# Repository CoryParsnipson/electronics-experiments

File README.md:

# electronics-experiments

Educational and experimental PCB designs for Raspberry pi related products and peripherals

## Project List

### [555-timer-pwm-with-digipot](./555-timer-pwm-with-digipot)

This is a hardware PWM output generator. This will give you a fixed frequency, variable duty-cycle PWM signal without using a microcontroller. This uses a 555-timer in astable oscillation mode that provides a 5% - 100% duty cycle. This allows you to control small motors and dim LED lights (see `ap5726-lcd-backlight-driver`).

### [ap5726-lcd-backlight-driver](./ap5726-lcd-backlight-driver)

This is a breakout board for testing the AP5726 white-LED driver (used for driving 5-7in LCD screen modules). This DC-DC converter is specifically designed to drive LEDs in series while supplying a constant 40mA current and up to 35V.

### [as01808ao-enclosure](./as01808ao-enclosure)

This is an experiment to mount an AS01808AO micro speaker to a PCB and have 3d printed enclosure parts bolted on. It works surprisingly well.

### [attiny-402-i2c-pwm-generator](./attiny-402-i2c-pwm-generator)

This is a project to use the new ATTiny series microcontroller to make an I2C controlled PWM signal that can be varied by frequency and duty cycle.

### [max98357-amp](./max98357-amp)

This is a design for a Class D speaker amplifier based on a [product by Adafruit](https://learn.adafruit.com/adafruit-max98357-i2s-class-d-mono-amp).

### [mipi-dsi-breakout](./mipi-dsi-breakout)

This is a pcb design that acts as an adapter board to hook up DSI signals coming from a LCD module with MIPI DSI interface to the raspberry pi.

### [retrocution-usb-hub](./retrocution-usb-hub)

The usb hub design uses an FE1.1s integrated USB 2.0 controller with the board layout heavily referenced from [Retrocution](https://www.retrocution.com/2020/01/15/easy-diy-tiny-usb-hub-for-raspberry-pi-projects/). Many thanks to Retrocution!

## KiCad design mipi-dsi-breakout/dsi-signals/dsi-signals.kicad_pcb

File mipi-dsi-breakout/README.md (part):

# mipi-dsi-breakout 

This design is intended to interface with different MIPI DSI LCD screens and route the DSI signals to a Raspberry Pi.

## KiCAD Version

Current version: KiCAD 9.0.3

This was originally made with KiCAD 9.0.3.

## Credits

Massive thanks to aBUGSworstnightmare and 6by9 of the Raspberry Pi Forums for help debugging and many factual and editorial corrections to this README. The debugging and driver/software stage of this project would not be possible without their help.

I am also thankful for the help and support from members of the SomthingAwful forums: babyeatingpsychopath, cakesmith handyman/bad dragon breath, Seat Safety Switch, Granite Octopus, Sgt Fox, ihafarm, HazCat, BlackTie, and many more.

## Sponsorship

The PCB fabrication for this project is sponsored by [PCBWay](https://www.pcbway.com/). PCBWay is a manufacturer of printed circuit boards and they also offer services such as PCB assembly, 3D printing plastic and metal, and much more. Their online quote system and thorough customer service made this design a breeze to order.

## Description

When working with microcontrollers or single board computers (SBC), you can buy "all-inclusive" LCD screen kits from electronics hobby stores that are basically plug and play. With this, the user experience is quite nice, needing only to plug in a video cable going from the LCD screen circuitry directly to the microcontroller or SBC. However, these kits leave little flexibilty terms of physical form factor, size and type of LCD screen, and price.

This project is an attempt to go beyond the beginner LCD peripherals offered by electronics hobby stores and interface directly with an LCD screen using custom peripheral circuitry. The hope is to increase the available LCD screens one can use beyond the small selection specifically available for a particular ecosystem of microcontroller or SBC products.

### Background and Context

An existing product like the [OSOYOO 5 inch DSI LCD Screen for Raspberry Pi](https://www.amazon.com/OSOYOO-Touchscreen-Monitor-Raspberry-800%C3%97480/dp/B0CWL7R8T4) was used as a reference base. This is a 5 inch screen that is designed to work out of the box with the Raspberry Pi family of products.

It is desirable for the following feaures:

* Built in touch screen
* Uses the DSI interface to transfer data (no need to use up an HDMI, USB, or GPIO pins to hook up)
* Supported out of the box by Raspberry Pi OS (no need to install external drivers)

It falls short due to:

* Relatively high price (~$50, too high for production runs)
* Large physical form factor (it is approximately 10 mm thick, permanently glued to a PCB, and contains metal standoffs which limit including it in a portable electronics device)
* Limited to 5 inch LCD screen and resolution from manufacturer

The objective of this project is to prototype something that could potentially replace this product while allowing one to swap the screen out and adjust the PCB design.

### Design Overview

For context into how this fits into a larger project, refer to the following block diagram:

Here we can see a motherboard for a Raspberry Pi Compute Module. This is a development board that you can use just like a regular computer once you hook up a keyboard, mouse, monitor, and power cord into it.

On the right, there is a section labeled "LCD Screen" (imagine that it is the OSOYOO screen). Described in 4 numbered functional blocks surrounding the screen component is the peripheral circuitry required to connect the LCD screen to the microcontroller.

Assuming that everything is built and working, we should be able to see the operating system graphical output on the LCD screen as if we were using it as a computer monitor. This project is a PCB implementation of the functional blocks labelled (1) and (4).

For information about implemting blocks (2) and (3), see the other projects in this repository, [ap5726-lcd-backlight-driver](/ap5726-lcd-backlight-driver) and [attiny-402-i2c-pwm-generator](/attiny-402-i2c-pwm-generator) respectively.

### LCD Screens Overview

The LCD screens this project is concerned with are mostly *Thin Film Transistor* (TFT) screens. See [this page](https://www.topwaydisplay.com/en/blog/how-tft-lcd-works-explained) to learn more about how TFT screens work. Essentially, TFT LCDs are a VLSI design that prints individual transistors on a transparent substrate that act as individual pixels. So the takeaway here is that it is not very simple or inexpensive to produce these, and that there are very expensive foundries needed to manufacture these like one would need to make CPUs and other integrated circuits, though a TFT screen does not require as small transistors nor is the design as complex as a CPU.

*Left: segmented (monochrome, big segments) Middle: dot matrix (monochrome, medium resolution) Right: TFT (graphical, transistors, RGB color)*

When searching for LCD screens one must be careful to specify which kind, between a segmented display, dot matrix, or a fully graphical screen. Here we want graphical displays.

Within the graphical LCD displays are Twisted Neumatic (TN) and In-Plane Switching (IPS) type displays with the difference being that IPS displays are more vibrant, brighter, and have a better viewing angle range than TN displays, which are older and cheaper than IPS displays.

There are also Organic LED (OLED) screens now, which are a different technology where VLSI LEDs are printed directly onto a substrate instead of whatever circuitry and electrodes TFT screens use. OLED screens are even more vibrant, have true black color, and supposedly use less energy because each pixel that is turned off does not consume power. These screens are better in every way, but are still relatively new and thus more expensive and less available. Now you have AMOLED screens which are minor improvements upon an OLED screen but mostly the same thing.

> NOTE: as of the time of this writing, if you try to buy an OLED screen from an electronics supplier, you may find very (physically) small, extremely low resolution, monochrome screens that have more in common with segmented displays or something you'd see in an old calculator. If you want a *graphical* OLED screen, you would need to specifically search for it, or try to get an AMOLED screen instead. Still, these are not as common as IPS displays.

### Overview of LCD Interfaces

If that wasn't complicated enough, one must also have to worry about the interface of the LCD screen, and there are many different interface protocols. Some of the more common ones:

* HDMI
* MIPI DSI
* LVDS
* SPI
* RGB/MCU/Parallel/DPI

#### HDMI

This might be the most popular screen interface. With an HDMI controller, the screen hooks up to a host using an HDMI cable. This makes it compatible with anything that supports the HDMI protocol, and not just a specific device. It also supports audio and input signals as well. This seems to be the most popular interface type for LCD screens around 5 inches in size, so it would give us the best options for screens.

Some of the disadvantages are the relatively complicated (and physically large) circuitry required, and the extra power consumption from converting from whatever format the LCD screen is in natively to HDMI. For these reasons, the search for screens for this project was limited to MIPI DSI.

> NOTE: in a "real" product development environment, what probably happens is that the designer will look for screens with the required attributes, and then integrate whatever interface the desired product was using afterwards. Going forward, this is probably a much better attitude than choosing the interface first.

#### MIPI DSI

MIPI DSI stands for *Mobile Industry Processor Interface Display Serial Interface*. For this project specifically, we have chosen to look for DSI screens exclusively because the DSI interface is convenient for Raspberry Pi products. Having a DSI screen uses less power, supports higher resolutions and refresh rates, low physical profile, and does not take up GPIO or other ports that could be used for other things. The DSI protocol is also meant for internal connectors for mobile and low power and physical small devices.

#### LVDS

"Low Voltage Differential Signaling" actually refers to the transmission method and not an entire protocol, so it is not quite equivelant to other things on this list. This term is usually kind of an umbrella term to refer to commercial or closed-source devices which have their own prioprietary protocol running on top of the LVDS transmission layer. This is common for larger screens such as for laptops and tablets. It is generally not recommended to use a screen that claims to use LVDS because it is hard to reverse engineer or find documentation on proprietary protocols, especially since they would be completely different across screens.

#### SPI

Serial Peripheral Interface (SPI) is a protocol used for many devices, not just screens. This is common for graphical LCD screens 3-4 inches and smaller, since the maximum data rate for SPI is not very fast. Even then, you may observe that the framerate is not very high due to the transfer rate limitations. Furthermore, an SPI screen will probably require more CPU overhead and power because the protocol is not designed specifically to transmit video. One good thing is that the interface and protocol is very simple, so it is very easy to integrate into a device as long as the screen is small and the framerate and resolution is not too large.

SPI devices usually hook in through GPIO pins.

#### RGB/MCU/Parallel/DPI

Display Parallel Interface (DPI) uses many more GPIO pins and as such the parallel configuration allows for much higher resolution or faster framerate than SPI devices do. It still suffers from similar power and CPU overhead limitations, but on the Raspberry Pi, there is a dedicated hardware block for driving DPI so aside from the GPIO usage, there is no overhead. For example, in a Raspberry Pi, hooking up a DPI screen may use almost all of the 40 available GPIO pins. This is not convenient if one wants to integrate multiple peripherals to the same Raspberry Pi or other GPIO limited device.

## Part Selection

### LCD Screen Parts

Finding LCD screen modules that are not part of a kit directly from manufacturers is tough. Lots of the supply is only available from China.

There were three main websites explored in my search for screens:

1. [Aliexpress](https://www.aliexpress.us)
   While not the most user friendly place, it contained the largest and relevant selection. I ended up buying all screens I wanted to try out from here. The "negotiation" process of talking to different salespeople to get a list of parts with the required specs was long and tedious. The pricing shown is not always accurate, but you can haggle with them. The price is dependent on the quantity you buy, which is usually a minimum of 500 or 1000 pieces, but you can order a few samples for a higher price for development (which is what I did).

1. [Waveshare](https://www.waveshare.com)
   This is more of a general electronics shop like Adafruit or SparkFun. For places like these, screen selection is very small, but the quality of parts is much better. The price is retail price, so not really ideal, but would still work for prototyping and development.

1. [BuyDisplay](https://www.buydisplay.com)
   This is another website that specializes in displays. The selection is large (but not as large as Aliexpress), and contains lots of unique parts.

#### Search Criteria

I was looking for a graphical, full color LCD screen that was around 5 inches across. Resolution around 480x800 or slightly higher is fine. The difficult part was finding parts with a MIPI DSI interface, which aren't very common especially on smaller screens. Looking at nits (>= 200) is a nice to have, to get an idea of whether or not the screen would be visible outdoors. A capactive touch screen was also a nice to have. If the screen comes with a touch panel, you can also ask them to customize the shape of the front lens/sticker if you order in bulk. This could be useful when putting together a complete product.

#### 4.3 Inch 480x800 MIPI DSI Display with CTP

The New Nintendo 3DS (non XL) top screen is about 4 inches across, and I think that is a nice size, so 4.3 inches wasn't out of the question. I bought one display I found at this size just to see if it would feel too small or not.

This was purchased from Dongguan Team off Aliexpress. The part number is `TST043WVBI-130` (or `TST043WVBI-130C` for the touch screen variant).

> NOTE: none of these screens are available anymore, but the suppliers probably have very similar products available for purchase. Suppliers are selling surplus screens from bigger customer orders, so inventory goes quickly and then parts change very often.

[Datasheet (without CTP)](/mipi-dsi-breakout/docs/TST043WVBI-130.pdf?raw=true)<br />
[Datasheet (just schematic with CTP)](/mipi-dsi-breakout/docs/TST043WVBI-130C.pdf?raw=true)

#### 5 Inch 720x1280 MIPI DSI Display with CTP

The TST050HDBS-80C was also purchased from Dongguan Team off Aliexpress.

An interesting thing about this is how large and lopsided the bezels on the touch panel are. It looks like this came from a small, budget tablet device.

Another aspect of this part is that it is a 4 lane MIPI DSI device. The Raspberry Pi I am using has one DSI port with 2 lanes and another with 4 lanes. There are displays out there that can be configured to support different numbers of lanes, so for those devices it may be possible to operate at either 2 or 4 lanes, as long as the proper configuration is in place. The number of lanes influences the amount of data or framerate that a screen can support. I bought 2 different 5 inch screens with differing resolutions to see if you could notice the difference.

[Datasheet](/mipi-dsi-breakout/docs/TST050HDBS-80C.pdf?raw=true)

#### 5 Inch 480x854 MIPI DSI Display

The ET050FW04-T was purchased from Shenzhen Eurotech Technology Co. Ltd. off Aliexpress.

The odd screen resolution comes from old cellphones, I think, which have a particularly elongated aspect ratio. This is the 2 lane MIPI DSI counterpart to the other DSI screen, and it doesn't come with a capacitive touch panel.

[Datasheet](/mipi-dsi-breakout/docs/ET050FW04-T.pdf?raw=true)

#### 6 Inch 720x1280 MIPI DSI Display

The ET060HD02-T was purchased from Shenzhen Eurotech Technology Co. Ltd. off Aliexpress.

> NOTE: while all the other screens on this list have a 0.5mm pitch FPC data cable, this screen has a 0.3mm pitch data cable!

The salesperson told me that they had a lot of 6 inch screens (an unusual size) that were from a 3d printer. Judging from the size and resolution, I'd say it was for a resin printer.

After playing on the Nintendo Switch for a while, I got the idea that maybe a larger screen would be nice too. The size of this screen is probably around the same as the Nintendo Switch Lite (though not nearly as nice) or slightly smaller than the original Nintendo Switch screen.

[Datasheet](/mipi-dsi-breakout/docs/ET060HD02-T.pdf?raw=true)

### Raspberry Pi Host Motherboard

The host for this project is a [Raspberry Pi CM3+ with 32 GB](https://www.raspberrypi.com/products/compute-module-3-plus/) of on board eMMC memory. This is the version of the Raspberry Pi intended for industrial applications and so cannot be used by itself.

The Raspberry Pi is paired with the [Compute Module IO Board Plus by Waveshare](https://www.waveshare.com/compute-module-io-board-plus.htm).

This project can be replicated with a different microcontroller, SBC, or PC, as long as the device supports DSI display ports. The compute module io board plus has a 22 pin DSI port with a specific pinout, so using a different product would most likely require modifying the designs in this repository to match.

[Here is a schematic](https://files.waveshare.com/upload/7/75/CM3-board.pdf) of the compute module IO board plus with the DSI port pinout.

### FFC Connector Selection

On the custom PCB, flat flexible cables (FFC)--also sometimes called zif (Zero-Insertion Force) connectors--comprise the majority of components. Aside from pin header, the only other components are 4.7 kOhm resistors for the I2C lines.

* [8pos 0.5mm connector (for 5 inch CTP cable)](https://www.digikey.com/en/products/detail/te-connectivity-amp-connectors/2328702-8/9565576)
* [10pos 0.5mm connector (for 4.3 inch CTP cable)](https://www.digikey.com/en/products/detail/te-connectivity-amp-connectors/1-2328702-0/9565577)
* [20pos 0.5mm connector (for 4.3 inch DSI cable)](https://www.digikey.com/en/products/detail/cvilux-usa/CF4220FH0R0-05-NH/15793107)
* [22pos 0.5mm connector (for RPI DSI port connector)](https://www.digikey.com/en/products/detail/cvilux-usa/CF4222FH0R0-05-NH/15793179)
* [25pos 0.3mm connector (for 6 inch DSI cable)](https://www.digikey.com/en/products/detail/cvilux-usa/CF5825DH0RA-NH/15793009)
* [30pos 0.5mm connector (for 5 inch DSI cable)](https://www.digikey.com/en/products/detail/amphenol-cs-fci/F3311A7H121030E200/15287516)
* [40pos 0.5mm connector (for 5 inch DSI cable)](https://www.digikey.com/en/products/detail/cvilux-usa/CF4240FH0R0-05-NH/15793119)

Exact parts are not necessary, many of the parts with the same specs have similar physical dimensions.

> WARNING: Careful about the 25pos connector, which is the only one that is 0.3mm pitch and its very different from the others.

### Other PCB components

You will also need a [22-pin 0.5mm FPC flx cable](https://www.digikey.com/en/products/detail/adafruit-industries-llc/6036/25589362), preferably at least 4.

Male pin header 2.54mm pitch. (At least 4 of 1x6, and optionally, 4 of 1x3 for the output signals).

And [4.7 kOhm surface mount resistors, 0805 (2012 Metric)](https://www.digikey.com/en/products/detail/te-connectivity-passive-product/CRGCQ0805F4K7/8576359), tolerance not important.

### Peripheral Electronics

To hook up all the input signals on this PCB via pin header, you will need:

* [ap5726-lcd-backlight-driver](/ap5726-lcd-backlight-driver)
* [attiny-402-i2c-pwm-generator](/attiny-402-i2c-pwm-generator)

These two circuits can be placed on a breadboard and hooked up to this PCB via jumper cables and pin header.

## PCB Layout

The main novelty of this project was learning to route high speed differential signals and complicated surface mount components.

This part in paricular was a very useful reference for MIPI DSI signal routing:

[PCB Artists - MIPI DSI PCB Layout Notes](https://pcbartists.com/design/pcb-design/mipi-dsi-pcb-layout-notes/)

### Differential High Speed Signal Background

The MIPI DSI protocol relies on high speed differential pair signals. To create a MIPI DSI LCD interface board, we will need to know how to route these signals. High speed, meaning signals that switch with frequency higher than 50 MHz. DSI transmission can reach speeds of up to 1Gbit/s per lane for devices using the 1.0 D-PHY, meaning up to 500 MHz clock, since it uses double data rate transfer. Devices using newer versions of the D-PHY may even run up to 2.5GHz. The clock speed is commonly proportional to the resolution and refresh speed of a particular display. In this project, we are targeting screens around 5 inches in size and slightly lower than HD resolution (480x800 or 1280x1024), so speeds will not be as high, but probably around the 50 - 100 MHz range.

The term differential pair refers to the fact that each signal is split into two complementary signals that are transmitted together. In other words, when one signal is high, the other signal is low. The destination device will receive both signals and take the difference between their values to recover the original signals.

Doing things this way allows one to transmit at lower voltages since the amplitude of each individual signal can be half the maximum value required, and also allows for higher data rates, and protection against electromagnetic interference (EMI).

The tradeoff is that it requires more board space for extra traces, specific geometric and PCB design constraints to accomodate the differential pair layout, and protocol overhead to recover the original signal.

What is of particular interest for this project are all the ways including differential pairs change the PCB layout constraints compared to "ordinary" non-high speed and non-differential signals. A design that is meant to include differential pairs must be done at the very start, because it involves all aspects of the board and layout.

#### Coupling

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
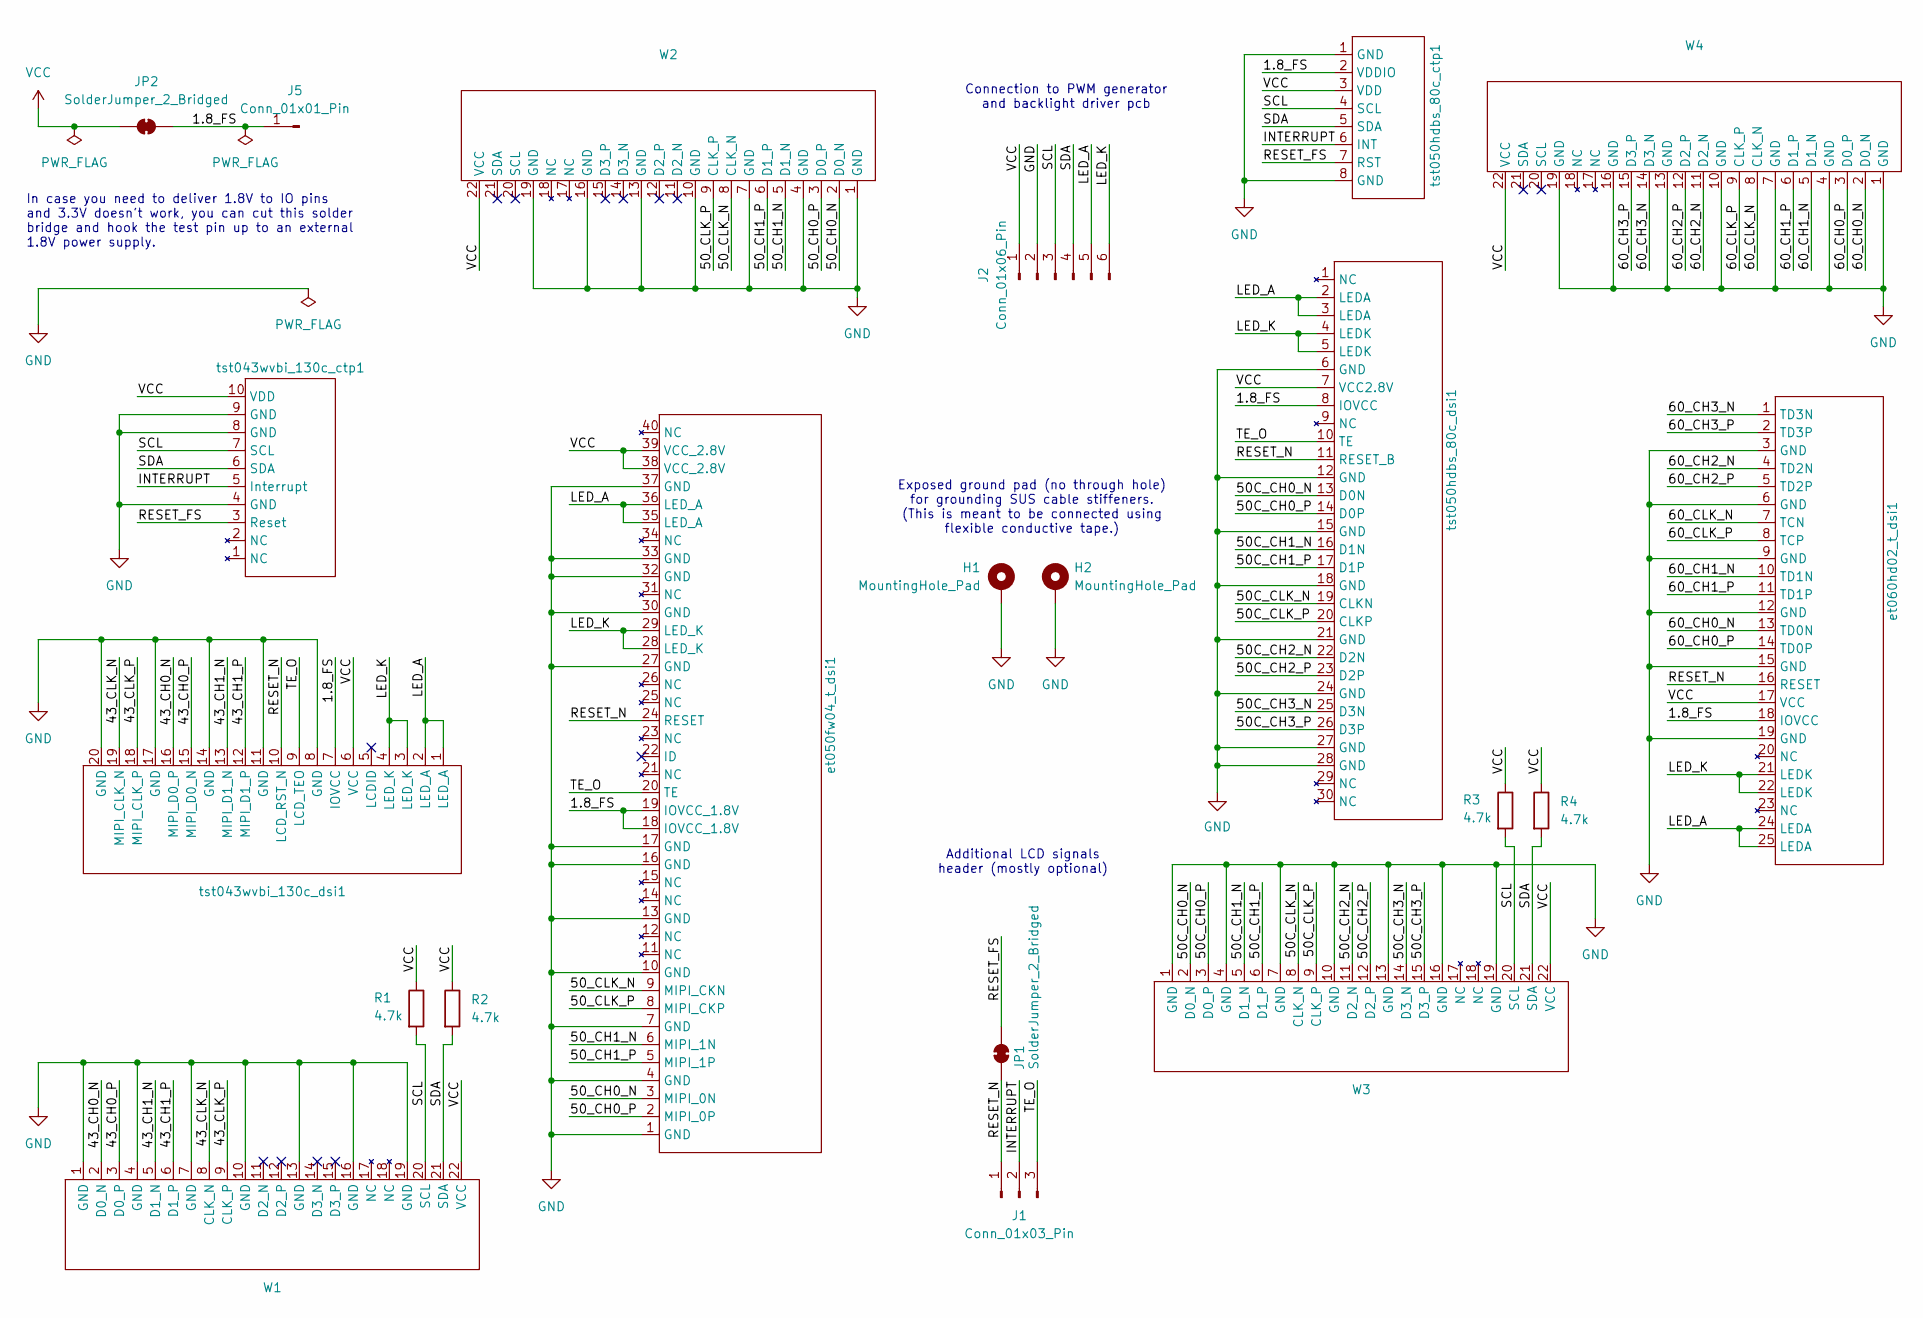
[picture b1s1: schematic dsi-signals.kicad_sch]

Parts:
H1, H2: MountingHole_Pad; sus-grounding-pad
J1: Conn_01x03_Pin; PinHeader_1x03_P2.54mm_Vertical
J2: Conn_01x06_Pin; PinHeader_1x06_P2.54mm_Vertical
J5: Conn_01x01_Pin; PinHeader_1x01_P2.54mm_Vertical
JP1, JP2: SolderJumper_2_Bridged; SolderJumper-2_P1.3mm_Bridged_Pad1.0x1.5mm
R1, R2, R3, R4: 4.7k; R_0805_2012Metric
W1, W2, W3, W4: Cvilux_CF4222FH0R0-05-NH_22pos-0.5mm-zif
et050fw04_t_dsi1: Cvilux_CF4240FH0R0-05-NH_40pos-0.5mm-zif
et060hd02_t_dsi1: Cvilux_CF5825DH0RA-NH_25pos-0.3mm-zif
tst043wvbi_130c_ctp1: TE_1-2328702-0_10pos-0.5mm-zif
tst043wvbi_130c_dsi1: Cvilux_CF4220FH0R0-05-NH_20pos-0.5mm-zif
tst050hdbs_80c_ctp1: TE_2328702_8pos-0.5mm-zif
tst050hdbs_80c_dsi1: Cvilux_CF4230FH0R0-05-NH_30pos-0.5mm-zif

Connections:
/1.8_FS: J5.1, JP2.1 (A), et050fw04_t_dsi1.18 (IOVCC_1.8V), et050fw04_t_dsi1.19 (IOVCC_1.8V), et060hd02_t_dsi1.18 (IOVCC), tst043wvbi_130c_dsi1.7 (IOVCC), tst050hdbs_80c_ctp1.2 (VDDIO), tst050hdbs_80c_dsi1.8 (IOVCC); also elsewhere on the board
/43_CH0_N: W1.2 (D0_N), tst043wvbi_130c_dsi1.16 (MIPI_D0_P)
/43_CH0_P: W1.3 (D0_P), tst043wvbi_130c_dsi1.15 (MIPI_D0_N)
/43_CH1_N: W1.5 (D1_N), tst043wvbi_130c_dsi1.13 (MIPI_D1_N)
/43_CH1_P: W1.6 (D1_P), tst043wvbi_130c_dsi1.12 (MIPI_D1_P)
/43_CLK_N: W1.8 (CLK_N), tst043wvbi_130c_dsi1.19 (MIPI_CLK_N)
/43_CLK_P: W1.9 (CLK_P), tst043wvbi_130c_dsi1.18 (MIPI_CLK_P)
/50C_CH0_N: W3.2 (D0_N), tst050hdbs_80c_dsi1.13 (D0N)
/50C_CH0_P: W3.3 (D0_P), tst050hdbs_80c_dsi1.14 (D0P)
/50C_CH1_N: W3.5 (D1_N), tst050hdbs_80c_dsi1.16 (D1N)
/50C_CH1_P: W3.6 (D1_P), tst050hdbs_80c_dsi1.17 (D1P)
/50C_CH2_N: W3.11 (D2_N), tst050hdbs_80c_dsi1.22 (D2N)
/50C_CH2_P: W3.12 (D2_P), tst050hdbs_80c_dsi1.23 (D2P)
/50C_CH3_N: W3.14 (D3_N), tst050hdbs_80c_dsi1.25 (D3N)
/50C_CH3_P: W3.15 (D3_P), tst050hdbs_80c_dsi1.26 (D3P)
/50C_CLK_N: W3.8 (CLK_N), tst050hdbs_80c_dsi1.19 (CLKN)
/50C_CLK_P: W3.9 (CLK_P), tst050hdbs_80c_dsi1.20 (CLKP)
/50_CH0_N: W2.2 (D0_N), et050fw04_t_dsi1.3 (MIPI_0N)
/50_CH0_P: W2.3 (D0_P), et050fw04_t_dsi1.2 (MIPI_0P)
/50_CH1_N: W2.5 (D1_N), et050fw04_t_dsi1.6 (MIPI_1N)
/50_CH1_P: W2.6 (D1_P), et050fw04_t_dsi1.5 (MIPI_1P)
/50_CLK_N: W2.8 (CLK_N), et050fw04_t_dsi1.9 (MIPI_CKN)
/50_CLK_P: W2.9 (CLK_P), et050fw04_t_dsi1.8 (MIPI_CKP)
/60_CH0_N: W4.2 (D0_N), et060hd02_t_dsi1.13 (TD0N)
/60_CH0_P: W4.3 (D0_P), et060hd02_t_dsi1.14 (TD0P)
/60_CH1_N: W4.5 (D1_N), et060hd02_t_dsi1.10 (TD1N)
/60_CH1_P: W4.6 (D1_P), et060hd02_t_dsi1.11 (TD1P)
/60_CH2_N: W4.11 (D2_N), et060hd02_t_dsi1.4 (TD2N)
/60_CH2_P: W4.12 (D2_P), et060hd02_t_dsi1.5 (TD2P)
/60_CH3_N: W4.14 (D3_N), et060hd02_t_dsi1.1 (TD3N)
/60_CH3_P: W4.15 (D3_P), et060hd02_t_dsi1.2 (TD3P)
/60_CLK_N: W4.8 (CLK_N), et060hd02_t_dsi1.7 (TCN)
/60_CLK_P: W4.9 (CLK_P), et060hd02_t_dsi1.8 (TCP)
/INTERRUPT: J1.2, tst043wvbi_130c_ctp1.5 (Interrupt), tst050hdbs_80c_ctp1.6 (INT)
/LED_A: J2.5, et050fw04_t_dsi1.35 (LED_A), et050fw04_t_dsi1.36 (LED_A), et060hd02_t_dsi1.24 (LEDA), et060hd02_t_dsi1.25 (LEDA), tst043wvbi_130c_dsi1.1 (LED_A), tst043wvbi_130c_dsi1.2 (LED_A), tst050hdbs_80c_dsi1.2 (LEDA), tst050hdbs_80c_dsi1.3 (LEDA)
/LED_K: J2.6, et050fw04_t_dsi1.28 (LED_K), et050fw04_t_dsi1.29 (LED_K), et060hd02_t_dsi1.21 (LEDK), et060hd02_t_dsi1.22 (LEDK), tst043wvbi_130c_dsi1.3 (LED_K), tst043wvbi_130c_dsi1.4 (LED_K), tst050hdbs_80c_dsi1.4 (LEDK), tst050hdbs_80c_dsi1.5 (LEDK)
/RESET_FS: JP1.2 (B), tst043wvbi_130c_ctp1.3 (Reset), tst050hdbs_80c_ctp1.7 (RST); also elsewhere on the board
/RESET_N: J1.1, JP1.1 (A), et050fw04_t_dsi1.24 (RESET), et060hd02_t_dsi1.16 (RESET), tst043wvbi_130c_dsi1.10 (LCD_RST_N), tst050hdbs_80c_dsi1.11 (RESET_B); also elsewhere on the board
/SCL: J2.3, R1.2, R3.2, W1.20 (SCL), W3.20 (SCL), tst043wvbi_130c_ctp1.7 (SCL), tst050hdbs_80c_ctp1.4 (SCL)
/SDA: J2.4, R2.2, R4.2, W1.21 (SDA), W3.21 (SDA), tst043wvbi_130c_ctp1.6 (SDA), tst050hdbs_80c_ctp1.5 (SDA)
/TE_O: J1.3, et050fw04_t_dsi1.20 (TE), tst043wvbi_130c_dsi1.9 (LCD_TEO), tst050hdbs_80c_dsi1.10 (TE)
GND: H1.1, H2.1, J2.2, W1.1 (GND), W1.4 (GND), W1.7 (GND), W1.10 (GND), W1.13 (GND), W1.16 (GND), W1.19 (GND), W2.1 (GND), W2.4 (GND), W2.7 (GND), W2.10 (GND), W2.13 (GND), W2.16 (GND), W2.19 (GND), W3.1 (GND), W3.4 (GND), W3.7 (GND), W3.10 (GND), W3.13 (GND), W3.16 (GND), W3.19 (GND), W4.1 (GND), W4.4 (GND), W4.7 (GND), W4.10 (GND), W4.13 (GND), W4.16 (GND), W4.19 (GND), et050fw04_t_dsi1.1 (GND), et050fw04_t_dsi1.4 (GND), et050fw04_t_dsi1.7 (GND), et050fw04_t_dsi1.10 (GND), et050fw04_t_dsi1.13 (GND), et050fw04_t_dsi1.16 (GND), et050fw04_t_dsi1.17 (GND), et050fw04_t_dsi1.27 (GND), et050fw04_t_dsi1.30 (GND), et050fw04_t_dsi1.32 (GND), et050fw04_t_dsi1.33 (GND), et050fw04_t_dsi1.37 (GND), et060hd02_t_dsi1.3 (GND), et060hd02_t_dsi1.6 (GND), et060hd02_t_dsi1.9 (GND), et060hd02_t_dsi1.12 (GND), et060hd02_t_dsi1.15 (GND), et060hd02_t_dsi1.19 (GND), tst043wvbi_130c_ctp1.4 (GND), tst043wvbi_130c_ctp1.8 (GND), tst043wvbi_130c_ctp1.9 (GND), tst043wvbi_130c_dsi1.8 (GND), tst043wvbi_130c_dsi1.11 (GND), tst043wvbi_130c_dsi1.14 (GND), tst043wvbi_130c_dsi1.17 (GND), tst043wvbi_130c_dsi1.20 (GND), tst050hdbs_80c_ctp1.1 (GND), tst050hdbs_80c_ctp1.8 (GND), tst050hdbs_80c_dsi1.6 (GND), tst050hdbs_80c_dsi1.12 (GND), tst050hdbs_80c_dsi1.15 (GND), tst050hdbs_80c_dsi1.18 (GND), tst050hdbs_80c_dsi1.21 (GND), tst050hdbs_80c_dsi1.24 (GND), tst050hdbs_80c_dsi1.27 (GND), tst050hdbs_80c_dsi1.28 (GND)
VCC: J2.1, R1.1, R2.1, R3.1, R4.1, W1.22 (VCC), W2.22 (VCC), W3.22 (VCC), W4.22 (VCC), et050fw04_t_dsi1.38 (VCC_2.8V), et050fw04_t_dsi1.39 (VCC_2.8V), et060hd02_t_dsi1.17 (VCC), tst043wvbi_130c_ctp1.10 (VDD), tst043wvbi_130c_dsi1.6 (VCC), tst050hdbs_80c_ctp1.3 (VDD), tst050hdbs_80c_dsi1.7 (VCC2.8V); also elsewhere on the board

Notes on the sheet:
Connection to PWM generator and backlight driver pcb
Exposed ground pad (no through hole) for grounding SUS cable stiffeners. (This is meant to be connected using flexible conductive tape.)
In case you need to deliver 1.8V to IO pins and 3.3V doesn't work, you can cut this solder bridge and hook the test pin up to an external 1.8V power supply.
Additional LCD signals header (mostly optional)

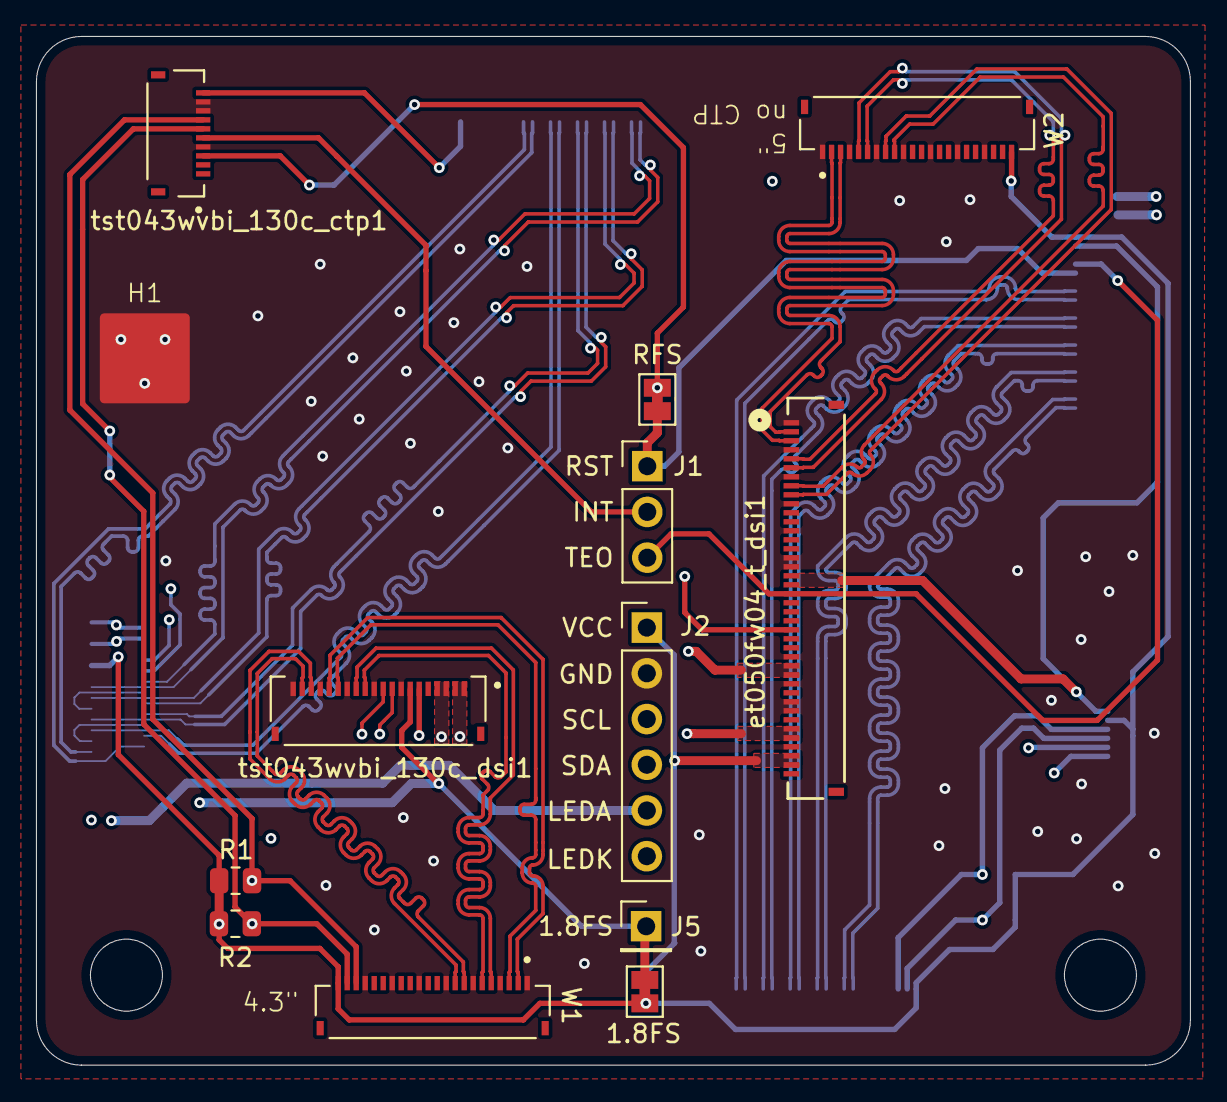
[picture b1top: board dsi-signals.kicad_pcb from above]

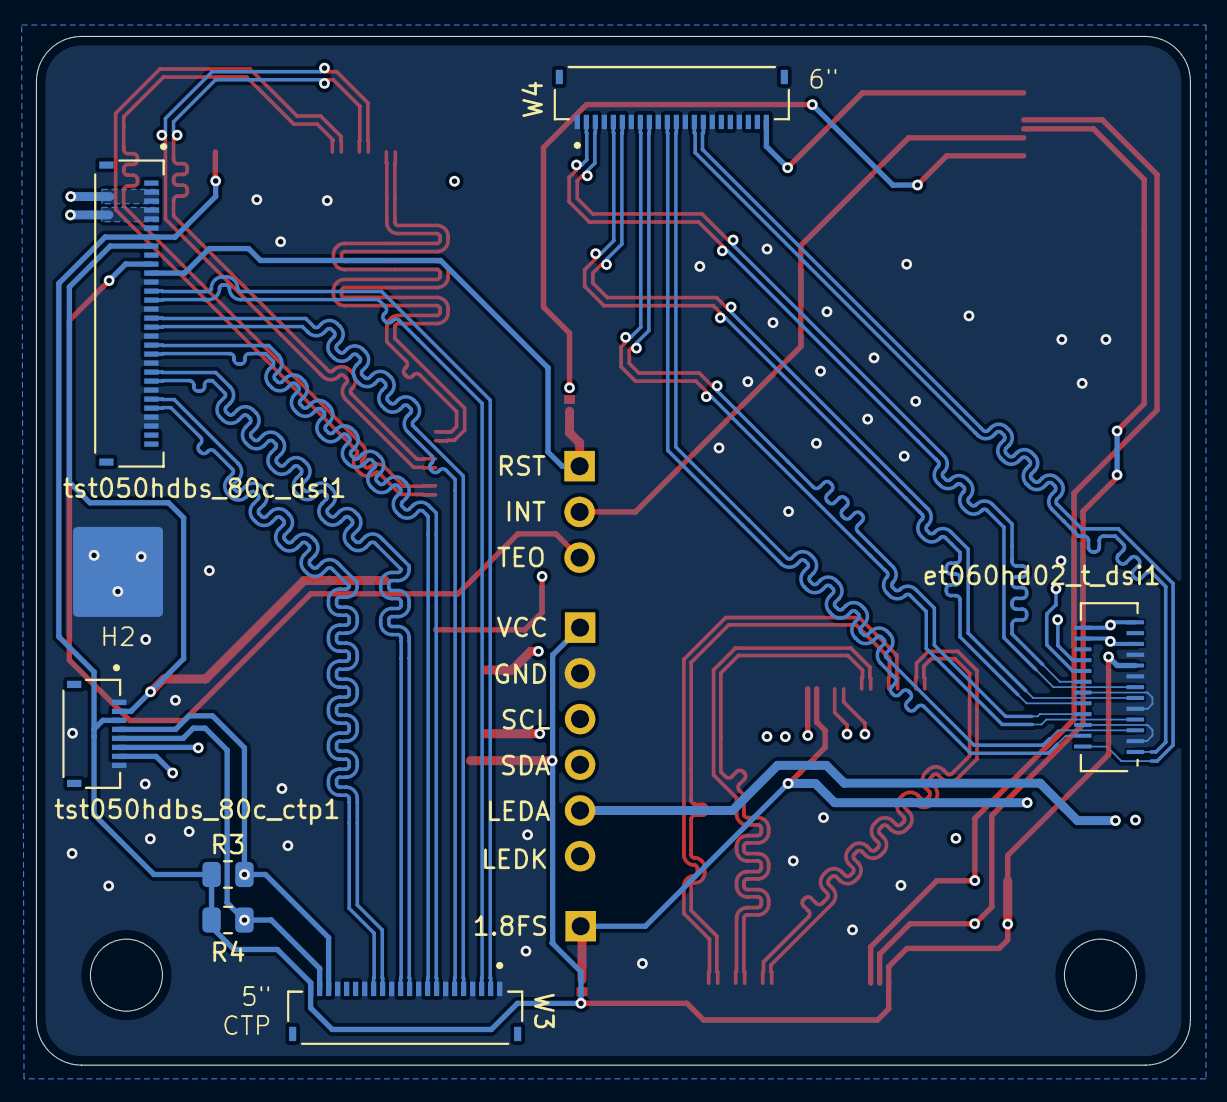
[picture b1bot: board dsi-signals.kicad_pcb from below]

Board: 4 copper layers, 64.1 x 57.2 mm, 21 parts (8 on the bottom side), 43 nets.

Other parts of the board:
1.8FS: SolderJumper_2_Bridged; SolderJumper-2_P1.3mm_Bridged_Pad1.0x1.5mm
RFS: SolderJumper_2_Bridged; SolderJumper-2_P1.3mm_Bridged_Pad1.0x1.5mm

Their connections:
/1.8_FS: 1.8FS.1 (A); also elsewhere on the board
/RESET_FS: RFS.2 (B); also elsewhere on the board
/RESET_N: RFS.1 (A); also elsewhere on the board
VCC: 1.8FS.2 (B); also elsewhere on the board

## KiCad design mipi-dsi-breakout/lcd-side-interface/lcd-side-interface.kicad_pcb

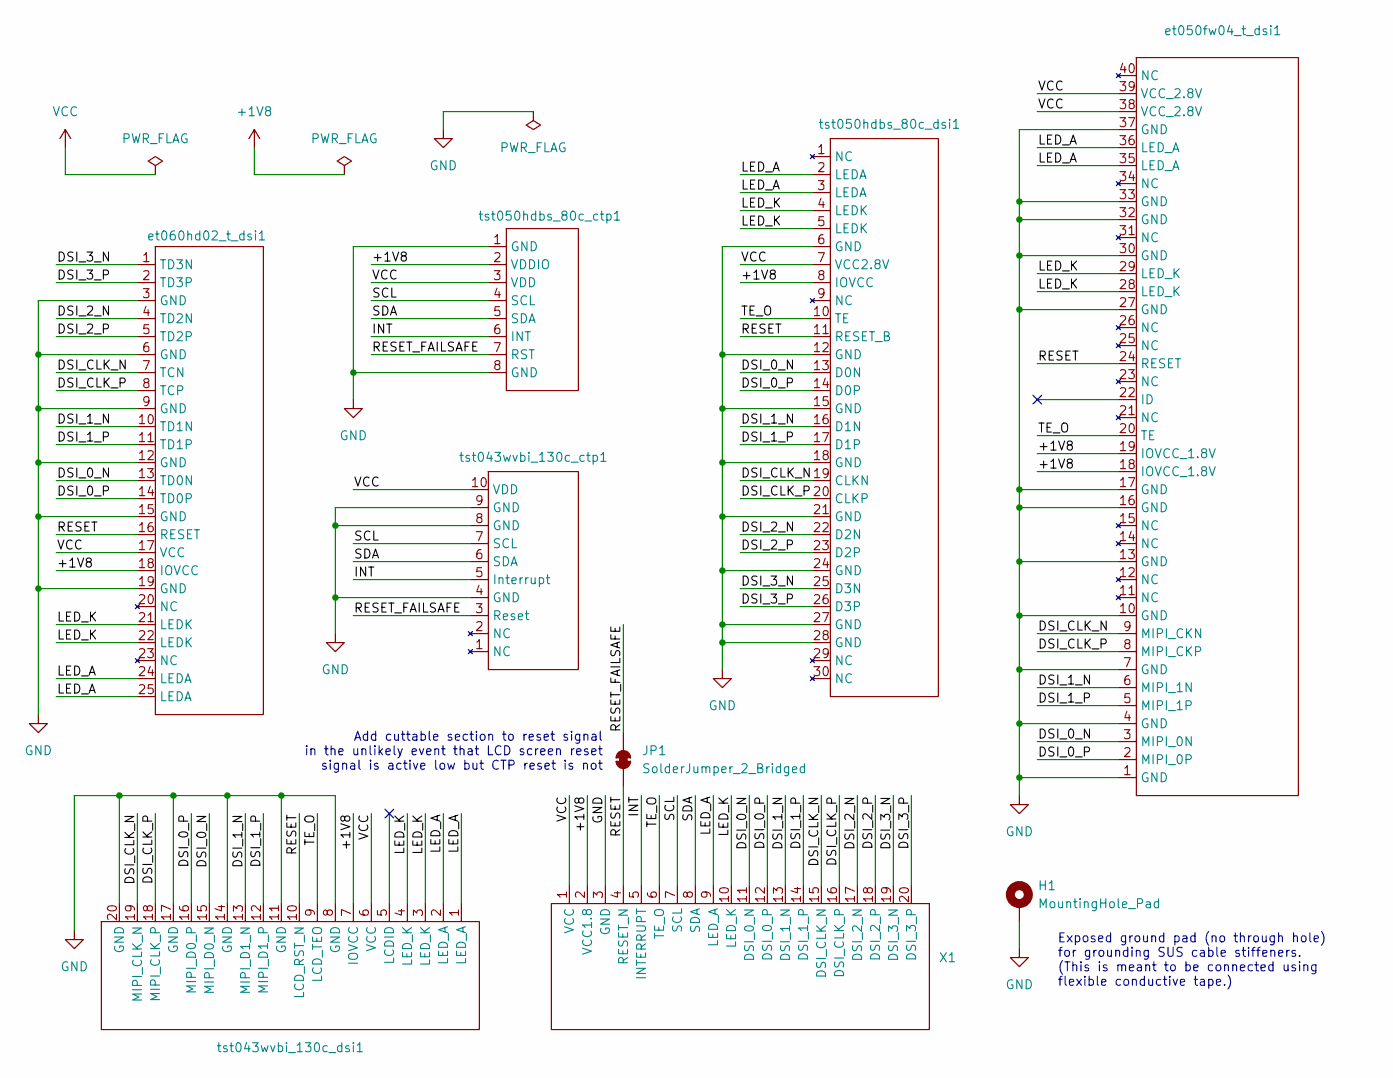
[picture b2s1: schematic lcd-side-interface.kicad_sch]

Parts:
H1: MountingHole_Pad; sus-grounding-pad
JP1: SolderJumper_2_Bridged; SolderJumper-2_P1.3mm_Bridged_Pad1.0x1.5mm
X1: PinHeader_1x20_P2.54mm_Vertical
et050fw04_t_dsi1: Cvilux_CF4240FH0R0-05-NH_40pos-0.5mm-zif
et060hd02_t_dsi1: Cvilux_CF5825DH0RA-NH_25pos-0.3mm-zif
tst043wvbi_130c_ctp1: TE_1-2328702-0_10pos-0.5mm-zif
tst043wvbi_130c_dsi1: Cvilux_CF4220FH0R0-05-NH_20pos-0.5mm-zif
tst050hdbs_80c_ctp1: TE_2328702_8pos-0.5mm-zif
tst050hdbs_80c_dsi1: Cvilux_CF4230FH0R0-05-NH_30pos-0.5mm-zif

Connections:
+1V8: X1.2 (VCC1.8), et050fw04_t_dsi1.18 (IOVCC_1.8V), et050fw04_t_dsi1.19 (IOVCC_1.8V), et060hd02_t_dsi1.18 (IOVCC), tst043wvbi_130c_dsi1.7 (IOVCC), tst050hdbs_80c_ctp1.2 (VDDIO), tst050hdbs_80c_dsi1.8 (IOVCC)
/DSI_0_N: X1.11 (DSI_0_N), et050fw04_t_dsi1.3 (MIPI_0N), et060hd02_t_dsi1.13 (TD0N), tst043wvbi_130c_dsi1.15 (MIPI_D0_N), tst050hdbs_80c_dsi1.13 (D0N)
/DSI_0_P: X1.12 (DSI_0_P), et050fw04_t_dsi1.2 (MIPI_0P), et060hd02_t_dsi1.14 (TD0P), tst043wvbi_130c_dsi1.16 (MIPI_D0_P), tst050hdbs_80c_dsi1.14 (D0P)
/DSI_1_N: X1.13 (DSI_1_N), et050fw04_t_dsi1.6 (MIPI_1N), et060hd02_t_dsi1.10 (TD1N), tst043wvbi_130c_dsi1.13 (MIPI_D1_N), tst050hdbs_80c_dsi1.16 (D1N)
/DSI_1_P: X1.14 (DSI_1_P), et050fw04_t_dsi1.5 (MIPI_1P), et060hd02_t_dsi1.11 (TD1P), tst043wvbi_130c_dsi1.12 (MIPI_D1_P), tst050hdbs_80c_dsi1.17 (D1P)
/DSI_2_N: X1.17 (DSI_2_N), et060hd02_t_dsi1.4 (TD2N), tst050hdbs_80c_dsi1.22 (D2N)
/DSI_2_P: X1.18 (DSI_2_P), et060hd02_t_dsi1.5 (TD2P), tst050hdbs_80c_dsi1.23 (D2P)
/DSI_3_N: X1.19 (DSI_3_N), et060hd02_t_dsi1.1 (TD3N), tst050hdbs_80c_dsi1.25 (D3N)
/DSI_3_P: X1.20 (DSI_3_P), et060hd02_t_dsi1.2 (TD3P), tst050hdbs_80c_dsi1.26 (D3P)
/DSI_CLK_N: X1.15 (DSI_CLK_N), et050fw04_t_dsi1.9 (MIPI_CKN), et060hd02_t_dsi1.7 (TCN), tst043wvbi_130c_dsi1.19 (MIPI_CLK_N), tst050hdbs_80c_dsi1.19 (CLKN)
/DSI_CLK_P: X1.16 (DSI_CLK_P), et050fw04_t_dsi1.8 (MIPI_CKP), et060hd02_t_dsi1.8 (TCP), tst043wvbi_130c_dsi1.18 (MIPI_CLK_P), tst050hdbs_80c_dsi1.20 (CLKP)
/INT: X1.5 (INTERRUPT), tst043wvbi_130c_ctp1.5 (Interrupt), tst050hdbs_80c_ctp1.6 (INT)
/LED_A: X1.9 (LED_A), et050fw04_t_dsi1.35 (LED_A), et050fw04_t_dsi1.36 (LED_A), et060hd02_t_dsi1.24 (LEDA), et060hd02_t_dsi1.25 (LEDA), tst043wvbi_130c_dsi1.1 (LED_A), tst043wvbi_130c_dsi1.2 (LED_A), tst050hdbs_80c_dsi1.2 (LEDA), tst050hdbs_80c_dsi1.3 (LEDA)
/LED_K: X1.10 (LED_K), et050fw04_t_dsi1.28 (LED_K), et050fw04_t_dsi1.29 (LED_K), et060hd02_t_dsi1.21 (LEDK), et060hd02_t_dsi1.22 (LEDK), tst043wvbi_130c_dsi1.3 (LED_K), tst043wvbi_130c_dsi1.4 (LED_K), tst050hdbs_80c_dsi1.4 (LEDK), tst050hdbs_80c_dsi1.5 (LEDK)
/RESET: JP1.1 (A), X1.4 (RESET_N), et050fw04_t_dsi1.24 (RESET), et060hd02_t_dsi1.16 (RESET), tst043wvbi_130c_dsi1.10 (LCD_RST_N), tst050hdbs_80c_dsi1.11 (RESET_B)
/RESET_FAILSAFE: JP1.2 (B), tst043wvbi_130c_ctp1.3 (Reset), tst050hdbs_80c_ctp1.7 (RST)
/SCL: X1.7 (SCL), tst043wvbi_130c_ctp1.7 (SCL), tst050hdbs_80c_ctp1.4 (SCL)
/SDA: X1.8 (SDA), tst043wvbi_130c_ctp1.6 (SDA), tst050hdbs_80c_ctp1.5 (SDA)
/TE_O: X1.6 (TE_O), et050fw04_t_dsi1.20 (TE), tst043wvbi_130c_dsi1.9 (LCD_TEO), tst050hdbs_80c_dsi1.10 (TE)
GND: H1.1, X1.3 (GND), et050fw04_t_dsi1.1 (GND), et050fw04_t_dsi1.4 (GND), et050fw04_t_dsi1.7 (GND), et050fw04_t_dsi1.10 (GND), et050fw04_t_dsi1.13 (GND), et050fw04_t_dsi1.16 (GND), et050fw04_t_dsi1.17 (GND), et050fw04_t_dsi1.27 (GND), et050fw04_t_dsi1.30 (GND), et050fw04_t_dsi1.32 (GND), et050fw04_t_dsi1.33 (GND), et050fw04_t_dsi1.37 (GND), et060hd02_t_dsi1.3 (GND), et060hd02_t_dsi1.6 (GND), et060hd02_t_dsi1.9 (GND), et060hd02_t_dsi1.12 (GND), et060hd02_t_dsi1.15 (GND), et060hd02_t_dsi1.19 (GND), tst043wvbi_130c_ctp1.4 (GND), tst043wvbi_130c_ctp1.8 (GND), tst043wvbi_130c_ctp1.9 (GND), tst043wvbi_130c_dsi1.8 (GND), tst043wvbi_130c_dsi1.11 (GND), tst043wvbi_130c_dsi1.14 (GND), tst043wvbi_130c_dsi1.17 (GND), tst043wvbi_130c_dsi1.20 (GND), tst050hdbs_80c_ctp1.1 (GND), tst050hdbs_80c_ctp1.8 (GND), tst050hdbs_80c_dsi1.6 (GND), tst050hdbs_80c_dsi1.12 (GND), tst050hdbs_80c_dsi1.15 (GND), tst050hdbs_80c_dsi1.18 (GND), tst050hdbs_80c_dsi1.21 (GND), tst050hdbs_80c_dsi1.24 (GND), tst050hdbs_80c_dsi1.27 (GND), tst050hdbs_80c_dsi1.28 (GND)
VCC: X1.1 (VCC), et050fw04_t_dsi1.38 (VCC_2.8V), et050fw04_t_dsi1.39 (VCC_2.8V), et060hd02_t_dsi1.17 (VCC), tst043wvbi_130c_ctp1.10 (VDD), tst043wvbi_130c_dsi1.6 (VCC), tst050hdbs_80c_ctp1.3 (VDD), tst050hdbs_80c_dsi1.7 (VCC2.8V)

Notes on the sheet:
Exposed ground pad (no through hole) for grounding SUS cable stiffeners. (This is meant to be connected using flexible conductive tape.)
Add cuttable section to reset signal in the unlikely event that LCD screen reset signal is active low but CTP reset is not

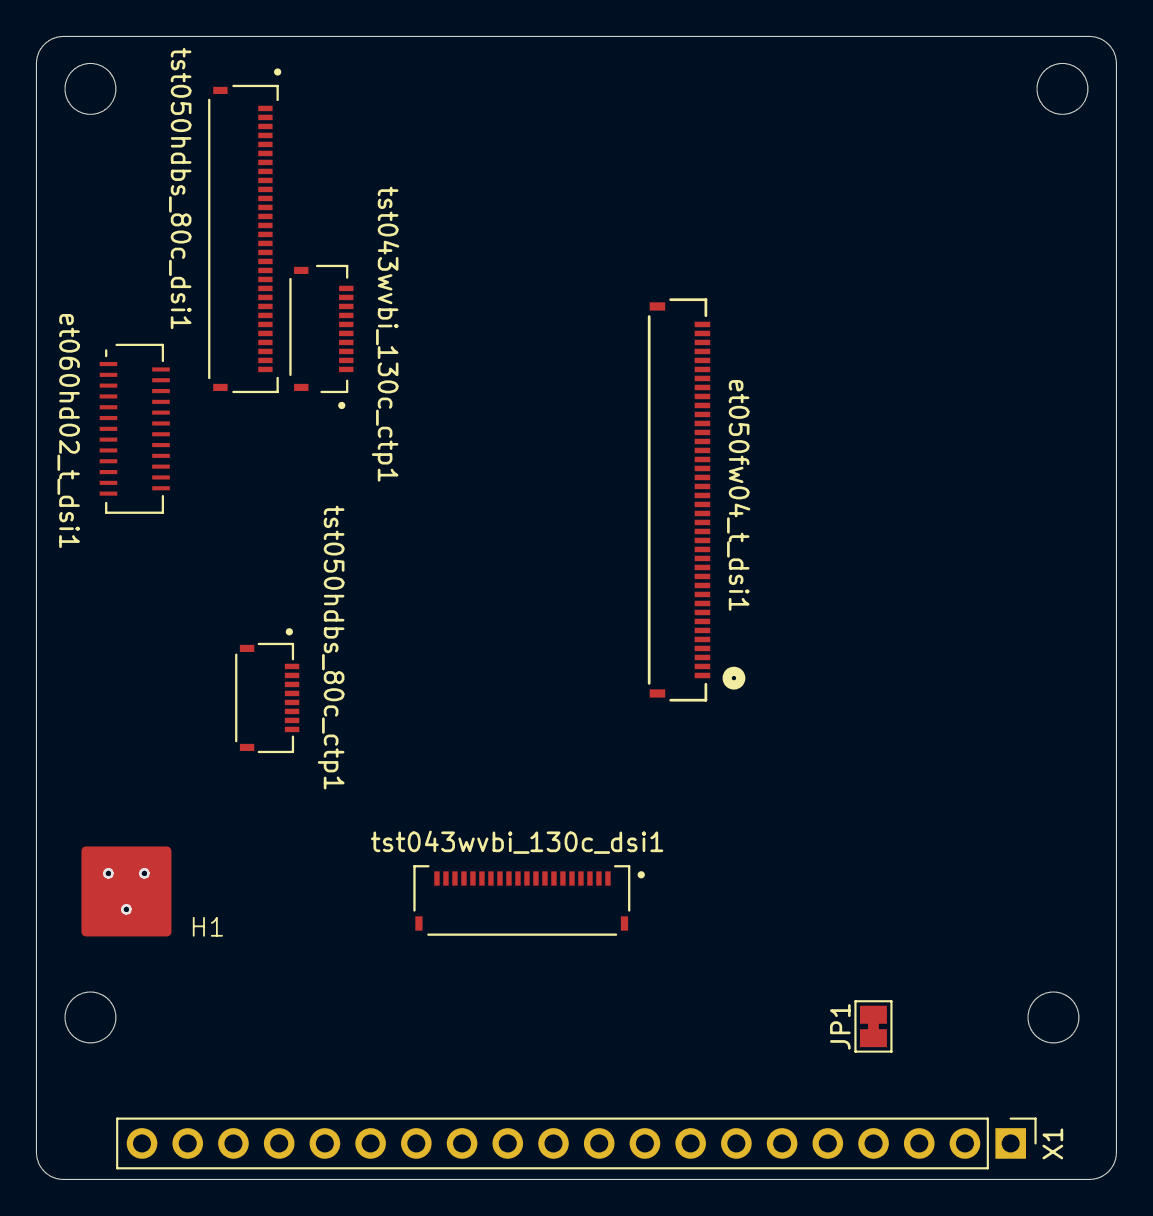
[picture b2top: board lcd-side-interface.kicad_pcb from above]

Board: 2 copper layers, 60.0 x 63.5 mm, 9 parts (0 on the bottom side), 21 nets.

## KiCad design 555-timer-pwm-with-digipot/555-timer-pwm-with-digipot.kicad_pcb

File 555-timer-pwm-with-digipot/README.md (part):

# 555-timer-pwm-with-digipot

This is a hardware pwm signal generator using a 555 timer. The design used here is one that uses two diodes attached to both ends of a potentiometer to make the duty cycle adjustable without changing the frequency. A twist on the usual design is that this project also uses a digital potentiometer (a.k.a. digipot) so that the duty cycle can be adjusted programmatically with a microcontroller via an I2C interface.

The purpose of this project is to provide digital access to an adjustable PWM signal to dim an lcd backlight driver. (See [ap5726-lcd-backlight-driver](../ap5726-lcd-backlight-driver).) The output signal of this project can be fed into the enable signal of an lcd backlight driver.

## Disclaimer

**This project is not recommended for real usage. This is not a very good way to generate a PWM signal compared to other methods.** See [Post Mortem](#post-mortem) for more detailed information.

## KiCAD Version

Current version: KiCAD 7.0.2.

This was originally made with KiCAD 7.0.2.

## Description

### PWM Generation using 555-timer in Astable Multivibrator Mode

A good explanation of how 555-timers work and how they operate in astable-multivibrator mode can be found at [How to Generate PWM Signal using 555 Timer IC](https://www.electronicshub.org/555-timer-pwm/), also listed as [1] in References. The author does a good job of explaining the functional logic and how it works. Basically, a 555-timer can be used to emit signal pulses at very specific, user-settable delays. This is known as "monostable" mode. A 555-timer can also be induced to oscillate like a clock signal by using feedback loops. This mode of operation is known as "astable" because it changes value by itself and "multi-vibrator" because it assumes different values.

Unfortunately, the author of [1] doesn't explain the PWM oscillator circuit in detail and really drops the ball at the end. I found a second page, [555 Circuits Part 1](https://www.electronics-tutorials.ws/waveforms/555-circuits-part-1.html#:~:text=Fully%20Independent%20555%20Oscillator&text=The%20timing%20period%20for%20both,without%20affecting%20the%20output%20frequency.), ([2] under References) that describes creating a PWM generator step-by-step starting from 555-timer astable mode. I am basing this project's circuit off of the "Fully Independent 555 Oscillator". [2] goes into much more detail about the circuit design. These two webpages together, I feel, are a very good primer into 555 circuits.

### Schematic for Project Design

The schematic was created by following the block diagram for the frequency independent 555-oscillator shown above. The [DS3502](https://www.analog.com/media/en/technical-documentation/data-sheets/DS3502.pdf) digipot is incorporated using the layout copied from the [Adafruit breakout board](https://www.adafruit.com/product/4286). The SDA and SCL signals require 10k pull up resistors. The A0 and A1 pins are hooked up to solder jumper pads for configurability. To change the I2C address, bridge the solder pins. The digipot also needs decoupling capacitors close to the V+ and Vin pins.

### PCB Layout Notes

* Decoupling caps for VCC and V+ pins of the digipot must be kept in the vicinity of their respective pins.
* SDA and SCL may benefit from ferrite beads. For a similar reason, I made sure that the ground plane on the back copper is behind both these traces as well as the digipot. Not sure if that's how it works though...

### Component Selection

#### Selection of C, R<sub>A</sub>, and R<sub>B</sub>

As explained by [1] and [2], the frequency and duty cycle that the oscillator will assume can be adjusted by selecting values for the three main components, the capacitor C, the fixed resistor R<sub>A</sub>, and the potentiometer R<sub>B</sub>.

The duty cycle is solely determined by the ratio of both resistors. Where R<sub>A</sub> is the "top" resistor, in series with the capacitor charging path, and R<sub>B</sub> is the bottom resistor, in series with the discharge path. As you can see from the formula, the duty cycle can theoretically go up to 100%, but R<sub>A</sub> is constraining the lower limit. We want this to be small.

* R<sub>A</sub> = 499 ohms
* R<sub>B</sub> = 10k ohms (total potentiometer resistance value)

These resistor values can give us a minimum 5% duty cycle. This most likely is not enough to completely turn off the LEDs. That is something I wish I knew before I started, that this particular design is not able to achieve a full duty cycle range. (As a note, other methods of generating PWM signals can achieve a full 0-100% duty cycle range.)

The last component to select is the value of the charging/discharging capacitor. This capacitor has the most influence on frequency.

The frequency we want should be <= 2 kHz, because this design is being made to control the enable signal of the AP5726 white led driver, and that chip is expecting an unfiltered PWM signal to be under 2 kHz. Going with the previous select resistor values, and a capacitor that is 0.1 uF, we get an expected frequency of 1190 Hz.

NOTE: One can still use this circuit and insert different valued components to change the duty cycle and frequency. This PCB layout uses 0805 (2012 metric) surface mount size resistors and capacitors.

The 1.25 constant in this formula comes from the inverse of 0.8, which itself had been changed from its original value of 0.693. This value is the ln(2), derived from some sort of manipulation of an exponential growth/decay formula. The site [2] mentions that the value was changed to 0.8 to account for using diodes with lower than usual threshold voltage. The derivation of this is not something I was able to find or come up with myself... In my experiment, this does not accurately reflect the empirically observed frequency that ended up being half the estimated value.

I was able to take that measurement and deduce that in my real component, the 1.25 factor is actually 0.546 for some reason.

This was done by taking the frequency measurement here and plugging that back into the frequency formula to solve for the "1.25" term. To get back to an expected 1190 Hz, one could halve the capacitor value to use 0.05 uF (50 nF) for a frequency of 1040.10 Hz. This is if 5V input voltage is used. If 3.3V will be used, the capacitor value may have to be reduced by a factor of 30%. (See [Post Mortem](#duty-cycle-range-is-unacceptable) for more information about this...)

#### 555-timer

The [TLC555CDR](https://www.digikey.com/en/products/detail/texas-instruments/TLC555CDR/276979) 555-timer is recommended for it's small form factor, low pin count, and ability to run at 3.3V.

#### Digipot

The [DS3502](https://www.analog.com/media/en/technical-documentation/data-sheets/DS3502.pdf) was used because it was available in breakout board form from Adafruit. However, in retrospect, the [MCP4561T-103E (Alternative digipot with low wiper resistance)](https://ww1.microchip.com/downloads/en/DeviceDoc/22107B.pdf) is a much better part with similar features. (See [Post Mortem](#digipot-wiper-resistance-cannot-be-ignored) for why this is.) **This PCB layout is not designed to work with the MCP4561T-103E as-is. The pins differ between the two chips.**

#### Diodes

This design needs fast switching small signal diodes, preferably with a low threshold voltage. The [BAT34W-TP schottky diodes](https://www.digikey.com/en/products/detail/micro-commercial-co/BAT43W-TP/717224) were chosen.

### Using a Digital Potentiometer

#### Pinout and Hookup

The SDA and SCL pins of the PCB should be hooked up to the corresponding SDA and SCL pins of your microcontroller of choice. I used a Raspberry Pi 3, as depicted in the above picture. One also needs to make sure the [I2C peripheral is enabled](https://www.raspberrypi-spy.co.uk/2014/11/enabling-the-i2c-interface-on-the-raspberry-pi/) and reboot the RPi. And that's all for the interfacing setup!

#### I2C interaction

One may use the available raspberry pi package "i2c-tools":

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
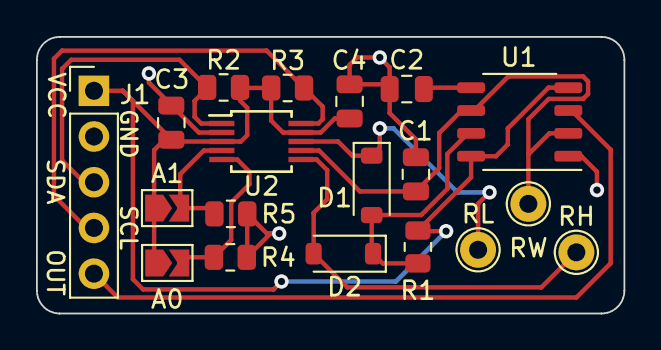
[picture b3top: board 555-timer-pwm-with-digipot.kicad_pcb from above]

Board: 2 copper layers, 32.6 x 15.4 mm, 19 parts (0 on the bottom side), 12 nets.

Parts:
A0, A1: SolderJumper-2_P1.3mm_Open_TrianglePad1.0x1.5mm
C1, C2, C3, C4: 0.1uF; C_0805_2012Metric
D1, D2: BAT43; D_SOD-123
J1: Conn_01x05_Pin; PinHeader_1x05_P2.54mm_Vertical
R1: 499; R_0805_2012Metric
R2, R3, R4, R5: 10k; R_0805_2012Metric
RH: TestPoint; TestPoint_THTPad_D2.0mm_Drill1.0mm
RL: TestPoint; TestPoint_THTPad_D2.0mm_Drill1.0mm
RW: TestPoint; TestPoint_THTPad_D2.0mm_Drill1.0mm
U1: SOIC-8_3.9x4.9mm_P1.27mm
U2: MSOP-10_3x3mm_P0.5mm

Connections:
/a0: A0.2 (B), R4.1, U2.5 (A0)
/a1: A1.2 (B), R5.1, U2.4 (A1)
/out: J1.5, U1.3 (OUT)
/scl: J1.4, R3.2, U2.10 (SCL)
/sda: J1.3, R2.2, U2.1 (SDA)
GND: C1.2, C2.2, C3.1, C4.2, J1.2, R4.2, R5.2, U1.1 (GND), U2.2 (GND)
unnamed: D1.2 (A), D2.1 (K), R1.2, U1.7 (DISCH)
unnamed: D1.1 (K), RL.1, U2.8 (RL)
unnamed: D2.2 (A), RH.1, U2.6 (RH)
unnamed: C2.1, U1.5 (CONT)
unnamed: C1.1, RW.1, U1.2 (TRIG), U1.6 (THRES), U2.7 (RW)
VCC: A0.1 (A), A1.1 (A), C3.2, C4.1, J1.1, R1.1, R2.1, R3.1, U1.4 (RESET), U1.8 (VCC), U2.3 (VCC), U2.9 (V+)
